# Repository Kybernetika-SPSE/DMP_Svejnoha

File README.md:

# Stanice pro monitorování okolního prostředí

## Zadání
Cílem projektu je navrhnout a následně vyrobit stanici složenou z LED displeje a senzorů, které budou sledovat vybrané parametry okolního prostředí. Zařízení bude obsahovat multifunkční displej a na základě uživatelských pokynů zobrazovat data. 

## Vedoucí práce
Jiří Švihla

## Harmonogram práce
- [x]   Zhotovení zadání MP (23. 9.)
- [/zadání maturitní práce/](zadani/DMP_zadani_SVEJNOHA.pdf)
- [x]   Výběr potřebných komponentů, seznámení se s problematikou a možnostmi programování LED
displeje (31. 10.)
- [/dílčí vypracování říjen/](dilci_vypracovani/SVEJNOHA_RIJEN.pdf)
- [x]   Návrh a realizace estetického a funkčního designu zařízení (28. 11.)
- [x]   Hardwarového zapojení senzorů a napájení (19. 12.)
- [/dílčí vypracování prosinec+listopad/](dilci_vypracovani/SVEJNOHA_LISTOPAD_A_PROSINEC.pdf)
- [x]   Programování displeje, zajištění možností využití zobrazení dat a ornamentů na displeji (30. 1.)
- [/dílčí vypracování leden/](dilci_vypracovani/SVEJNOHA_LEDEN.pdf)
- [ ]   Kompletace zařízení a testování (27. 2.)
- [ ]   Zpracování dokumentace (24. 3.)

## Termín odevzdání
31. března 2025

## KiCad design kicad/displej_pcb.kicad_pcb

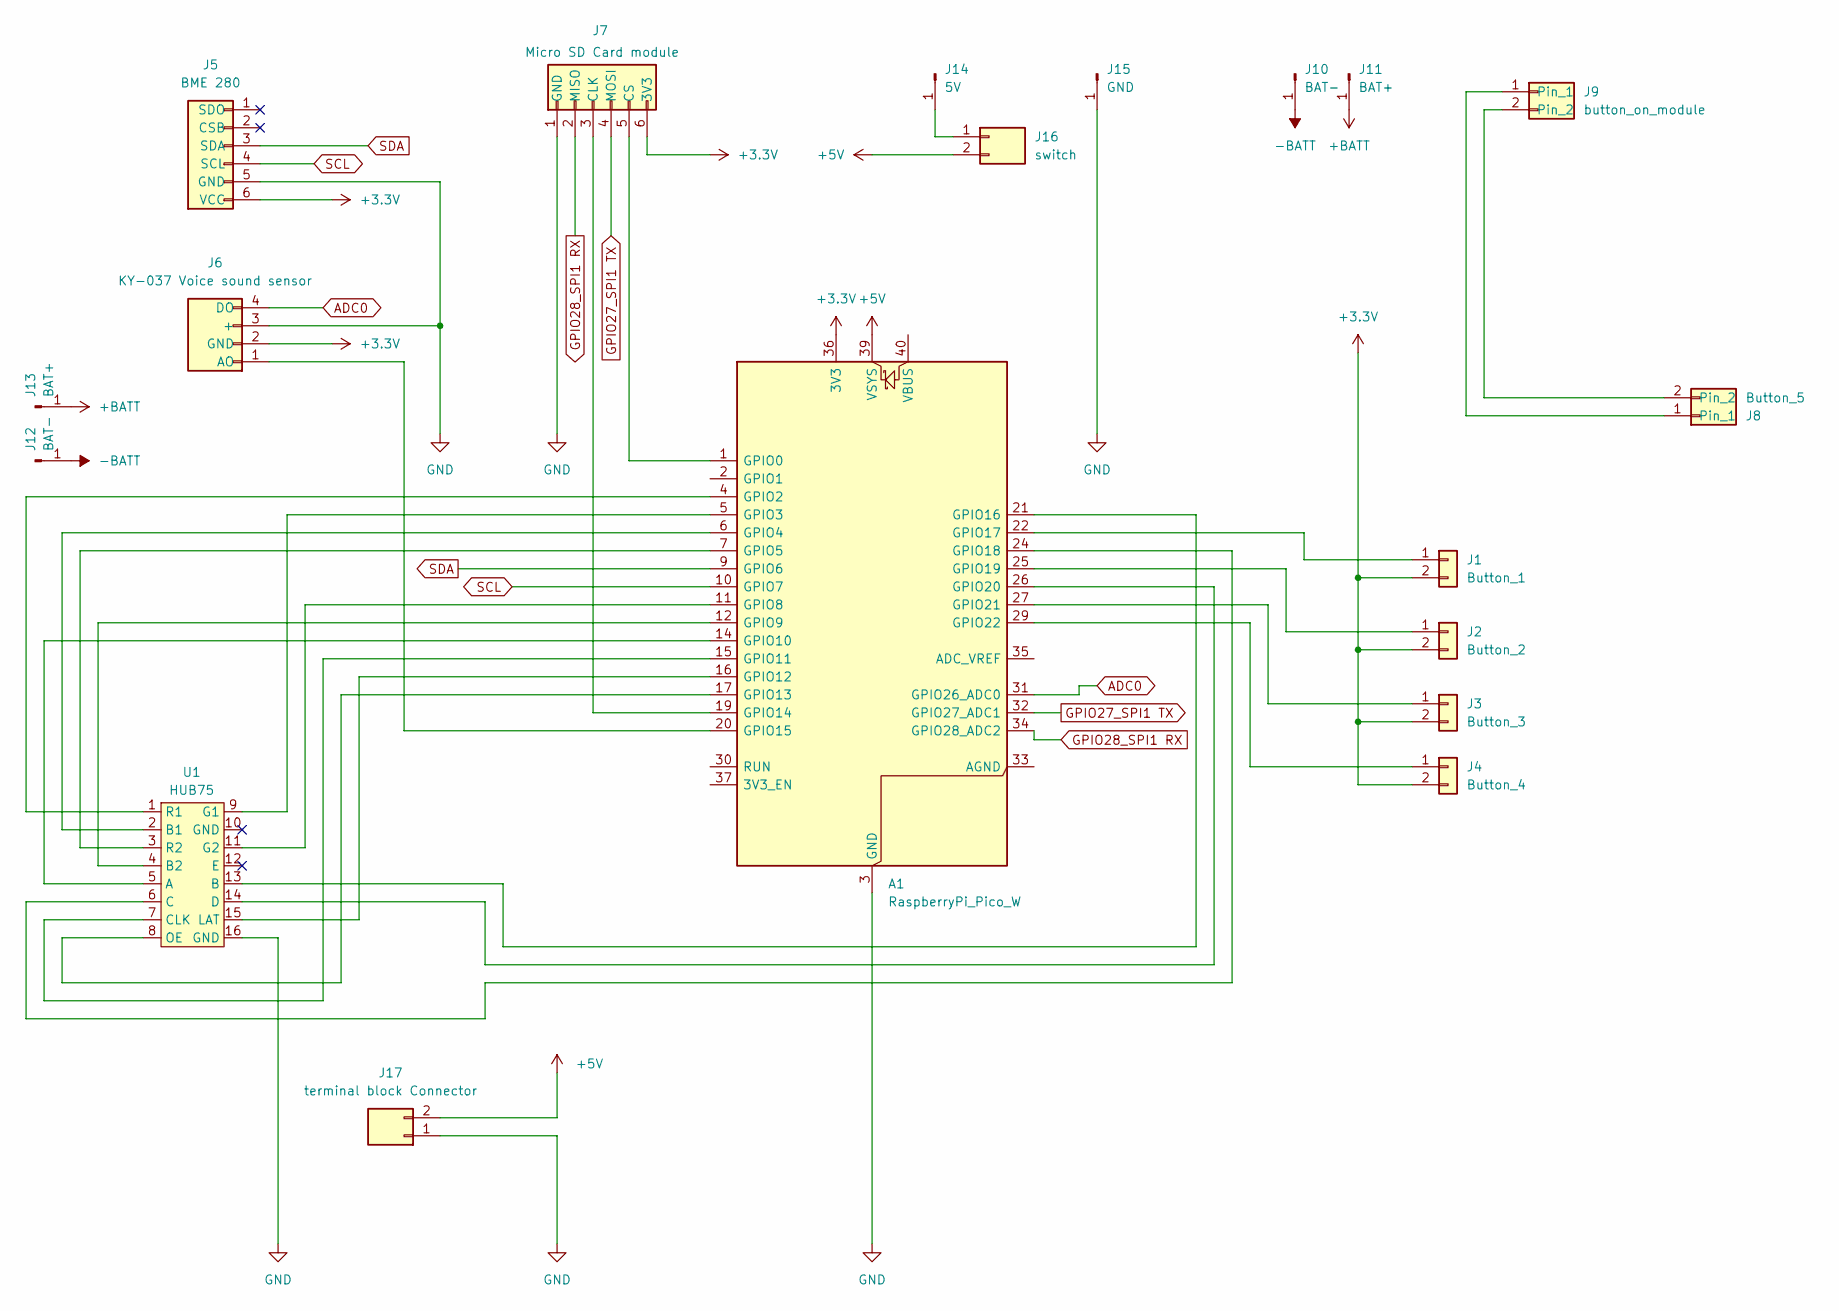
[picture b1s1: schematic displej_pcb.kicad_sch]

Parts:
A1: RaspberryPi_Pico_W; RaspberryPi_Pico_Common
J1: Button_1; buttons_solder_pins
J2: Button_2; buttons_solder_pins
J3: Button_3; buttons_solder_pins
J4: Button_4; buttons_solder_pins
J5: BME 280; PinHeader_1x06_P2.54mm_Vertical
J6: KY-037 Voice sound sensor; PinHeader_1x04_P2.54mm_Vertical
J7: Micro SD Card module; PinHeader_1x06_P2.54mm_Vertical
J8: Button_5; buttons_solder_pins
J9: button_on_module; solder_pads_2
J10, J12: BAT-; SolderWirePad_big
J11, J13: BAT+; SolderWirePad_big
J14: 5V; SolderWirePad_1x01_SMD_1x2mm
J15: GND; SolderWirePad_1x01_SMD_1x2mm
J16: switch; solder_pads_2
J17: terminal block Connector; JST_NV_B02P-NV_1x02_P5.00mm_Vertical
U1: HUB75; hub75

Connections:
+3.3V: A1.36 (3V3), J1.2, J2.2, J3.2, J4.2, J5.6 (VCC), J6.2 (GND), J7.6 (3V3)
+5V: A1.39 (VSYS), J16.2, J17.2
+BATT: J11.1, J13.1
-BATT: J10.1, J12.1
ADC0: A1.31 (GPIO26_ADC0), J6.4 (DO)
GND: A1.3 (GND), A1.8 (GND), A1.13 (GND), A1.18 (GND), A1.23 (GND), A1.28 (GND), A1.38 (GND), J5.5 (GND), J6.3 (+), J7.1 (GND), J15.1, J17.1, U1.16 (GND)
GPIO27_SPI1 TX: A1.32 (GPIO27_ADC1), J7.4 (MOSI)
GPIO28_SPI1 RX: A1.34 (GPIO28_ADC2), J7.2 (MISO)
unnamed: A1.1 (GPIO0), J7.5 (CS)
unnamed: A1.4 (GPIO2), U1.1 (R1)
unnamed: A1.5 (GPIO3), U1.9 (G1)
unnamed: A1.6 (GPIO4), U1.2 (B1)
unnamed: A1.7 (GPIO5), U1.3 (R2)
unnamed: A1.11 (GPIO8), U1.11 (G2)
unnamed: A1.12 (GPIO9), U1.4 (B2)
unnamed: A1.14 (GPIO10), U1.5 (A)
unnamed: A1.15 (GPIO11), U1.7 (CLK)
unnamed: A1.16 (GPIO12), U1.15 (LAT)
unnamed: A1.17 (GPIO13), U1.8 (OE)
unnamed: A1.19 (GPIO14), J7.3 (CLK)
unnamed: A1.20 (GPIO15), J6.1 (AO)
unnamed: A1.21 (GPIO16), U1.13 (B)
unnamed: A1.22 (GPIO17), J1.1
unnamed: A1.24 (GPIO18), U1.6 (C)
unnamed: A1.25 (GPIO19), J2.1
unnamed: A1.26 (GPIO20), U1.14 (D)
unnamed: A1.27 (GPIO21), J3.1
unnamed: A1.29 (GPIO22), J4.1
unnamed: J8.1, J9.1
unnamed: J8.2, J9.2
unnamed: J14.1, J16.1
SCL: A1.10 (GPIO7), J5.4 (SCL)
SDA: A1.9 (GPIO6), J5.3 (SDA)

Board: 2 copper layers, 19 parts (0 on the bottom side), 33 nets, no tracks yet.

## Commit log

2024-09-26 úprava readme
2024-09-26 aktualizace rm
2024-09-26 Create DOKUMENTACE
2024-10-30 Update README.md
    update 30/10/2024
2024-10-30 Rename SVEJNOHA_RIJEN.pdf to dilci_vypracovani/SVEJNOHA_RIJEN.pdf
2024-11-28 Create kicad
2024-12-05 Create a
2025-04-07 Create ahoj
2025-04-07 Create cc
2025-04-07 Create kod
